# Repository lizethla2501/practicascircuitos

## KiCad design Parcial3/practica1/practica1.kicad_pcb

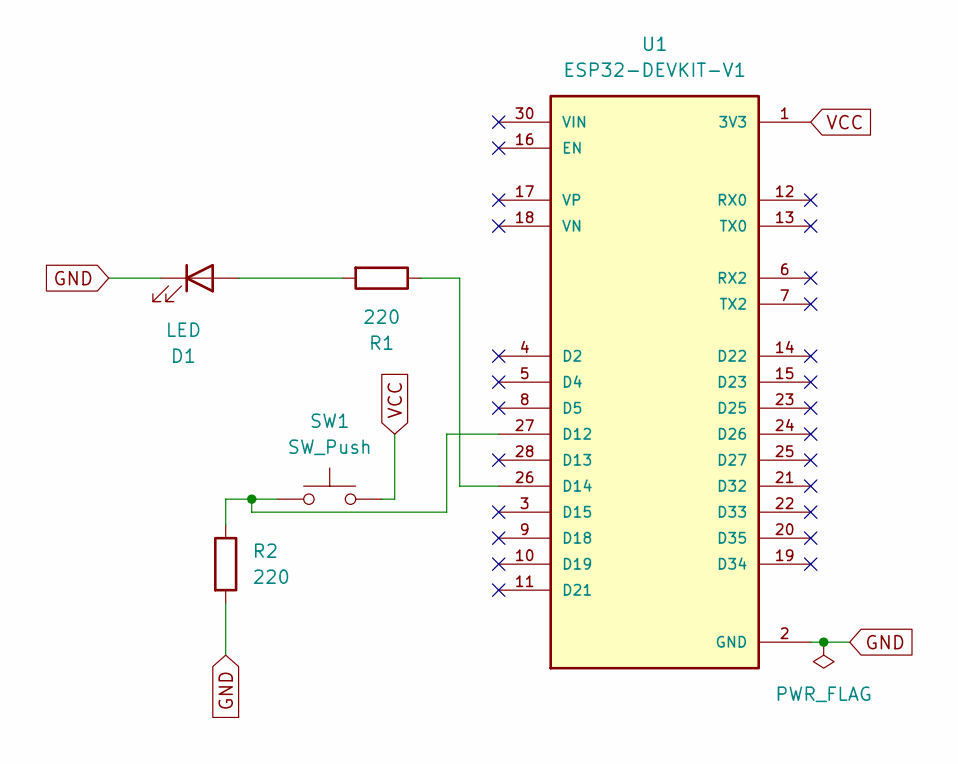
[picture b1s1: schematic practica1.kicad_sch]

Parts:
D1: LED; LED_0805_2012Metric
R1, R2: 220; R_0805_2012Metric
SW1: SW_Push; SW_Push_SPST_NO_Alps_SKRK
U1: ESP32-DEVKIT-V1; ESP32_DEVKIT_V1; PARTREV N/A

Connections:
GND: D1.1 (K), R2.2, U1.2 (GND), U1.29 (GND)
unnamed: D1.2 (A), R1.2
unnamed: R2.1, SW1.1, U1.27 (D12)
unnamed: R1.1, U1.26 (D14)
VCC: SW1.2, U1.1 (3V3)

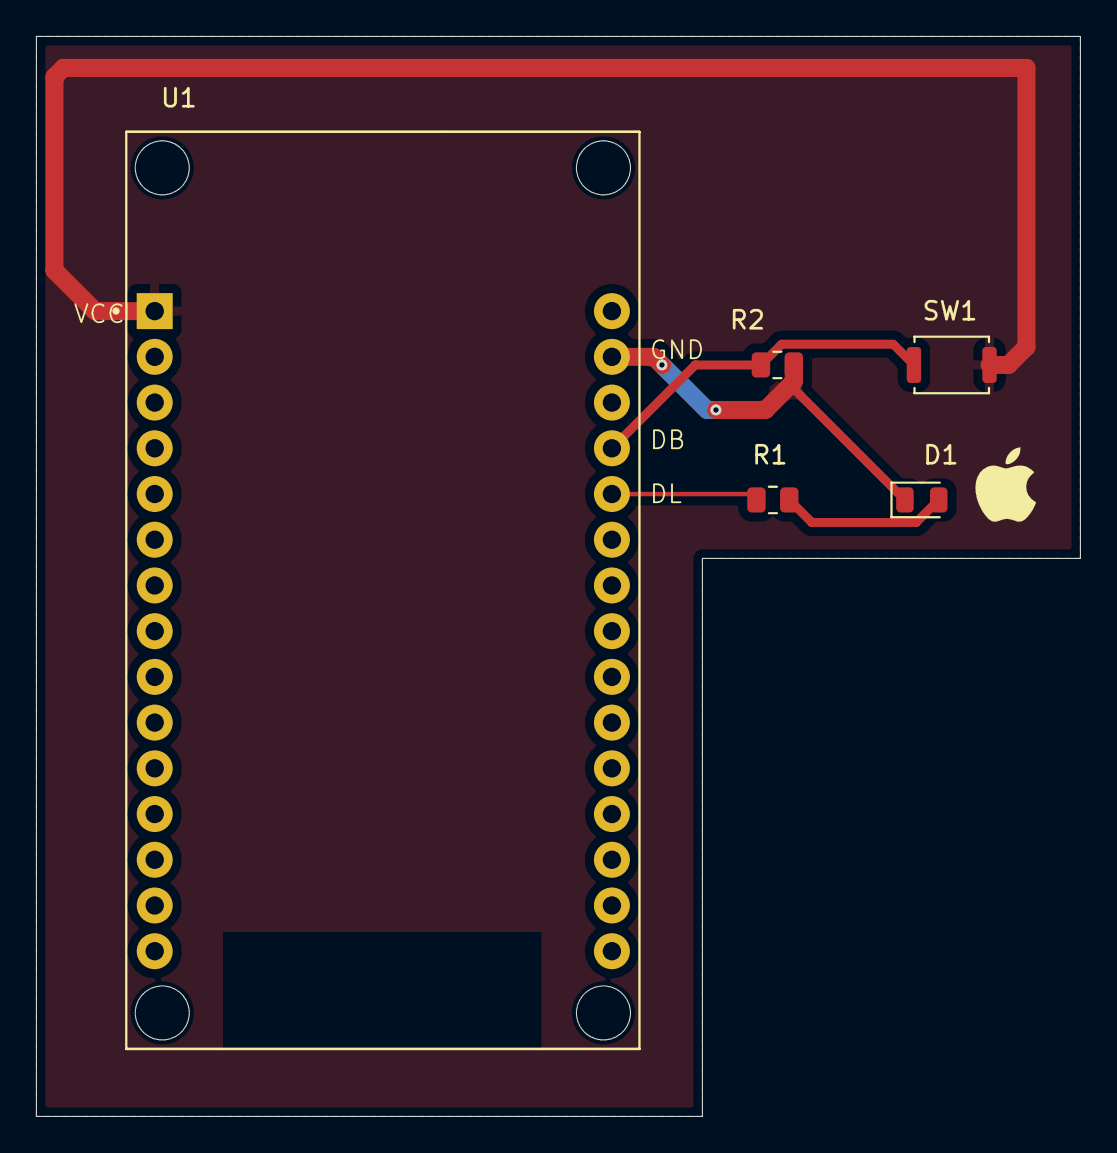
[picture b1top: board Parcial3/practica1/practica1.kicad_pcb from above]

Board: 2 copper layers, 58.0 x 60.0 mm, 5 parts (0 on the bottom side), 5 nets.

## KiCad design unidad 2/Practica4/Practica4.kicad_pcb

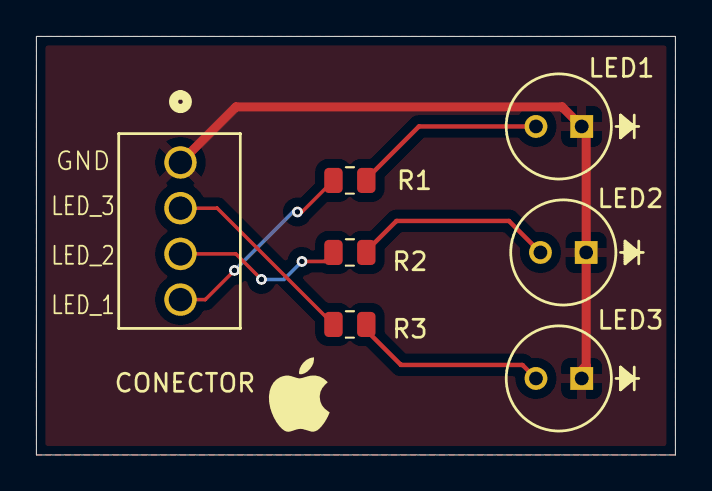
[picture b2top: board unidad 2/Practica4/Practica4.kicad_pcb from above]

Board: 2 copper layers, 35.5 x 23.2 mm, 7 parts (0 on the bottom side), 7 nets.

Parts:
CONECTOR: OSTVN04A150; TerminalBlock_CONN_OSTVN04A150_OST
LED1, LED2, LED3: LED; LED_LTL-4233_LTO
R1, R2, R3: 220; R_0805_2012Metric

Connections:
GND: CONECTOR.1, LED1.1 (K), LED2.1 (K), LED3.1 (K)
unnamed: LED1.2 (A), R1.2
unnamed: LED2.2 (A), R2.2
unnamed: LED3.2 (A), R3.2
unnamed: CONECTOR.2, R3.1
unnamed: CONECTOR.3, R2.1
unnamed: CONECTOR.4, R1.1

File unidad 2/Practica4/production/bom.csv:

Designator,Footprint,Quantity,Value,LCSC Part #
CONECTOR,TerminalBlock_CONN_OSTVN04A150_OST,1,OSTVN04A150,
"LED1, LED2, LED3",LED_LTL-4233_LTO,3,LED,
"R1, R2, R3",0805,3,220,

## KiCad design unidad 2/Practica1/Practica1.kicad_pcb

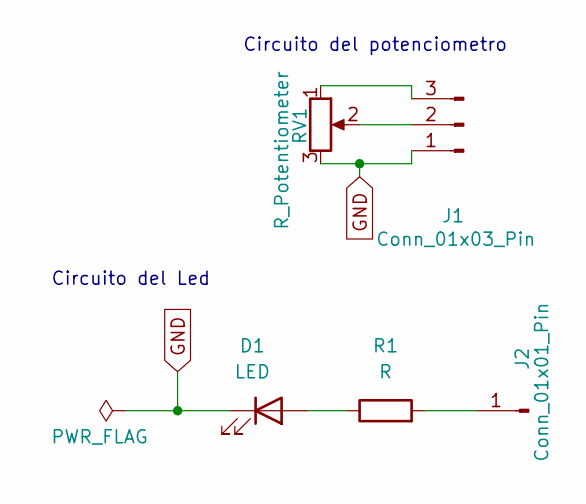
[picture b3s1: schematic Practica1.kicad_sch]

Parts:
D1: LED; LED_0805_2012Metric
J1: Conn_01x03_Pin; PinHeader_1x03_P2.54mm_Vertical
J2: Conn_01x01_Pin; PinHeader_1x01_P2.54mm_Vertical
R1: R; R_0805_2012Metric
RV1: R_Potentiometer; Potentiometer_Bourns_3339P_Vertical_HandSoldering

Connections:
GND: D1.1 (K), J1.1, RV1.3
unnamed: D1.2 (A), R1.1
unnamed: J1.2, RV1.2
unnamed: J1.3, RV1.1
unnamed: J2.1, R1.2

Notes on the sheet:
Circuito del Led
Circuito del potenciometro

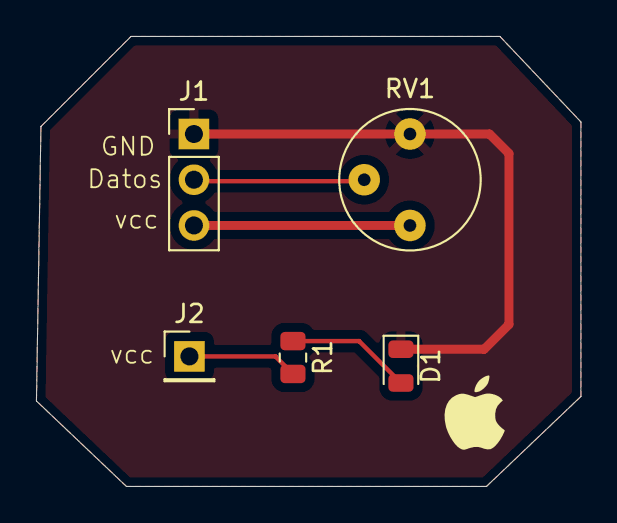
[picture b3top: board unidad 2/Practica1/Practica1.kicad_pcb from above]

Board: 2 copper layers, 30.2 x 25.0 mm, 5 parts (0 on the bottom side), 5 nets.

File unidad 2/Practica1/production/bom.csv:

Designator,Footprint,Quantity,Value,LCSC Part #
D1,0805,1,LED,
J1,PinHeader_1x03_P2.54mm_Vertical,1,Conn_01x03_Pin,
J2,PinHeader_1x01_P2.54mm_Vertical,1,Conn_01x01_Pin,
R1,0805,1,R,
RV1,Potentiometer_Bourns_3339P_Vertical_HandSoldering,1,R_Potentiometer,

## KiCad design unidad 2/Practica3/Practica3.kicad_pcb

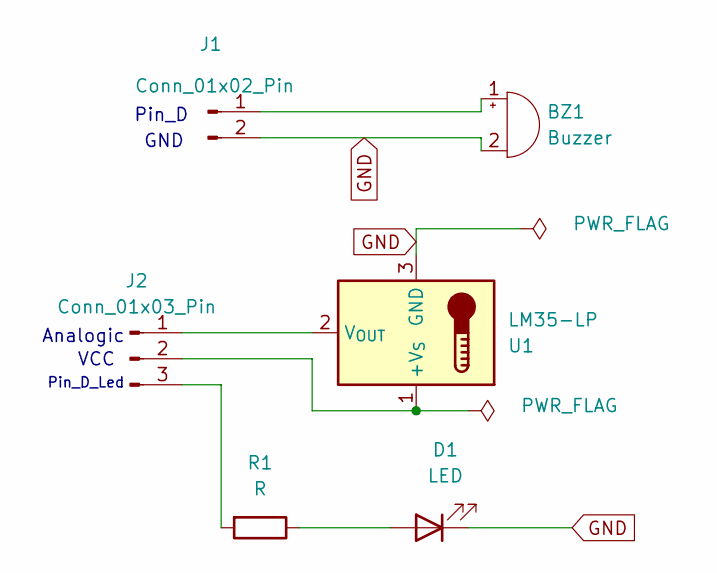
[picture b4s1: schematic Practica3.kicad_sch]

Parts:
BZ1: Buzzer; Buzzer_12x9.5RM7.6
D1: LED; LED_0805_2012Metric
J1: Conn_01x02_Pin; PinHeader_1x02_P2.54mm_Vertical
J2: Conn_01x03_Pin; PinHeader_1x03_P2.54mm_Vertical
R1: R; R_0805_2012Metric
U1: LM35-LP; TO-92_Inline

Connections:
GND: BZ1.2 (-), D1.1 (K), J1.2, U1.3 (GND)
unnamed: BZ1.1 (+), J1.1
unnamed: D1.2 (A), R1.1
unnamed: J2.1, U1.2 (V_{OUT})
unnamed: J2.2, U1.1 (+V_{S})
unnamed: J2.3, R1.2

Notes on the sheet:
Pin_D_Led
Analogic
VCC
GND
Pin_D

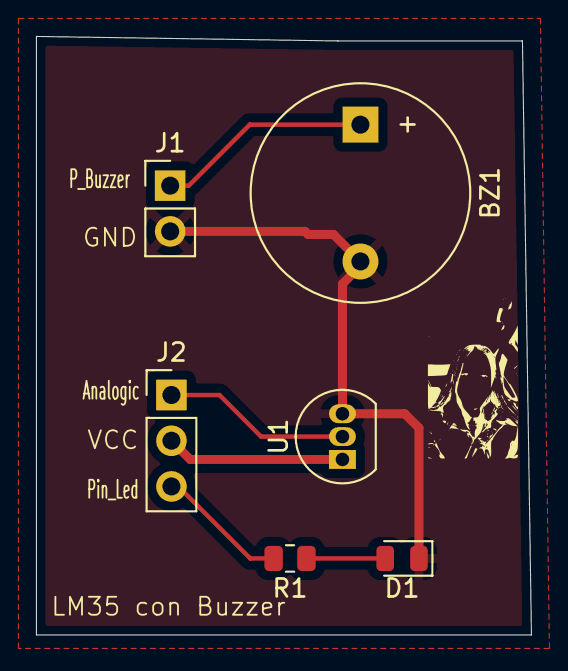
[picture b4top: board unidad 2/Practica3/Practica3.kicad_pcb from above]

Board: 2 copper layers, 27.5 x 33.2 mm, 6 parts (0 on the bottom side), 6 nets.

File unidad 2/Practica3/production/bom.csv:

Designator,Footprint,Quantity,Value,LCSC Part #
BZ1,Buzzer_12x9.5RM7.6,1,Buzzer,
D1,0805,1,LED,
J1,PinHeader_1x02_P2.54mm_Vertical,1,Conn_01x02_Pin,
J2,PinHeader_1x03_P2.54mm_Vertical,1,Conn_01x03_Pin,
R1,0805,1,R,
U1,TO-92_Inline,1,LM35-LP,

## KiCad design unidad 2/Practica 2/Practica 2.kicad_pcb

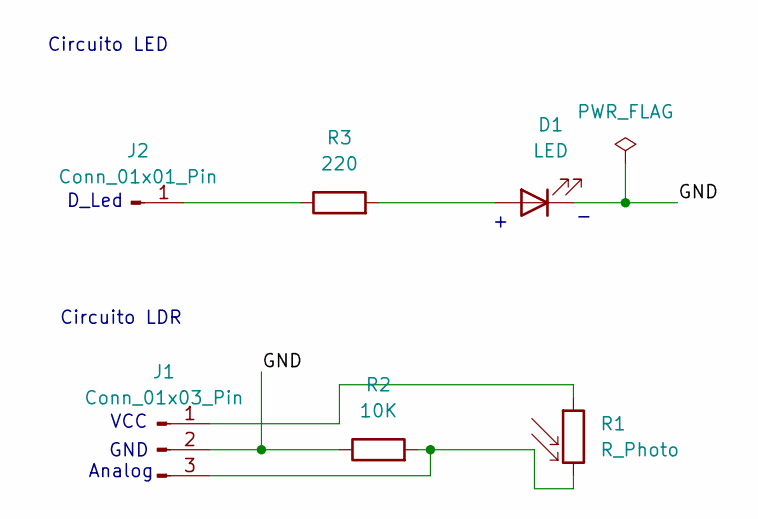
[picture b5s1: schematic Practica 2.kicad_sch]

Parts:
D1: LED; LED_0805_2012Metric
J1: Conn_01x03_Pin; PinHeader_1x03_P2.54mm_Vertical
J2: Conn_01x01_Pin; PinHeader_1x01_P2.54mm_Vertical
R1: R_Photo; R_LDR_5.1x4.3mm_P3.4mm_Vertical
R2: 10K; R_0805_2012Metric
R3: 220; R_0805_2012Metric

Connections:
/GND: D1.1 (K), J1.2, R2.1
unnamed: D1.2 (A), R3.2
unnamed: J1.1, R1.1
unnamed: J1.3, R1.2, R2.2
unnamed: J2.1, R3.1

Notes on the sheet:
Circuito LDR
Circuito LED
VCC
Analog
D_Led
GND

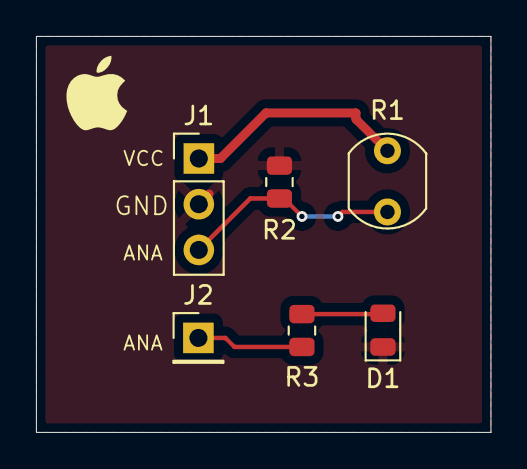
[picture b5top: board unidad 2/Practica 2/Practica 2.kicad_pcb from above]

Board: 2 copper layers, 25.2 x 22.0 mm, 6 parts (0 on the bottom side), 5 nets.

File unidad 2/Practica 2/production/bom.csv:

Designator,Footprint,Quantity,Value,LCSC Part #
D1,0805,1,LED,
J1,PinHeader_1x03_P2.54mm_Vertical,1,Conn_01x03_Pin,
J2,PinHeader_1x01_P2.54mm_Vertical,1,Conn_01x01_Pin,
R1,R_LDR_5.1x4.3mm_P3.4mm_Vertical,1,R_Photo,
R2,0805,1,10K,
R3,0805,1,220,

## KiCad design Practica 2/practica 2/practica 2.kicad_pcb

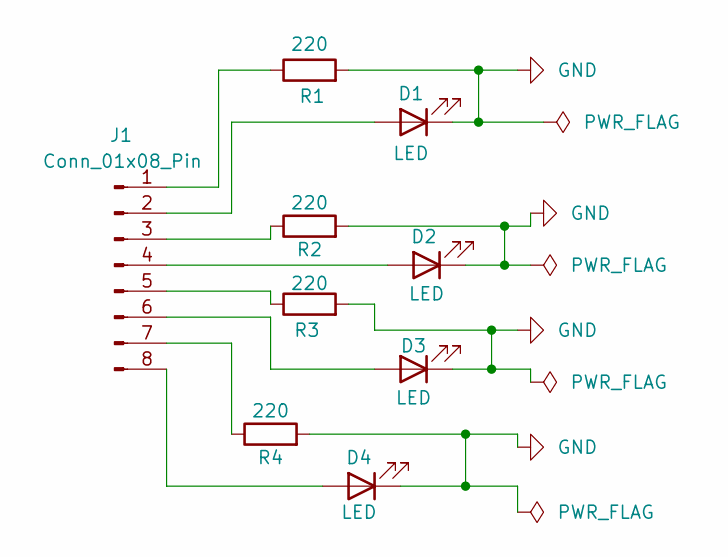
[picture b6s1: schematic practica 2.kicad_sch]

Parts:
D1, D2, D3, D4: LED; LED_0805_2012Metric
J1: Conn_01x08_Pin; PinHeader_1x08_P2.54mm_Vertical
R1, R2, R3, R4: 220; R_0805_2012Metric

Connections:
GND: D1.1 (K), D2.1 (K), D3.1 (K), D4.1 (K), R1.2, R2.2, R3.2, R4.2
unnamed: D1.2 (A), J1.2
unnamed: D2.2 (A), J1.4
unnamed: D3.2 (A), J1.6
unnamed: D4.2 (A), J1.8
unnamed: J1.1, R1.1
unnamed: J1.3, R2.1
unnamed: J1.5, R3.1
unnamed: J1.7, R4.1

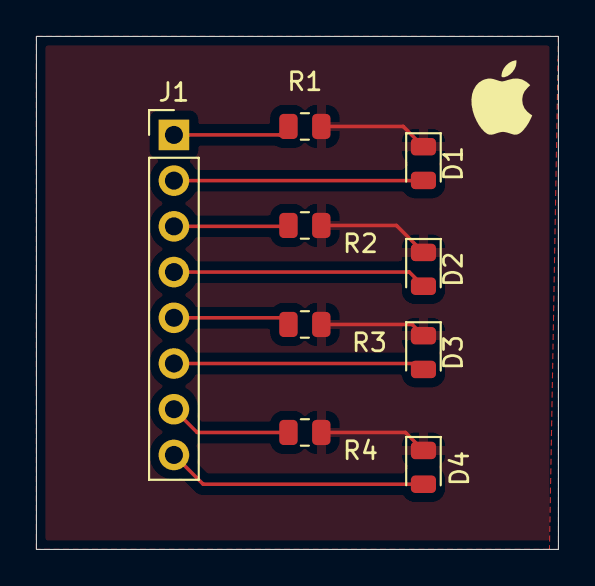
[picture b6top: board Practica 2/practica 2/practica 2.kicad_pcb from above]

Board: 2 copper layers, 29.0 x 28.5 mm, 9 parts (0 on the bottom side), 9 nets.

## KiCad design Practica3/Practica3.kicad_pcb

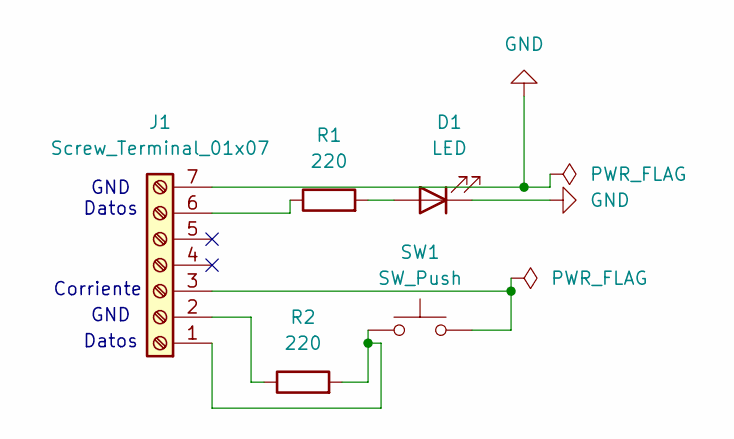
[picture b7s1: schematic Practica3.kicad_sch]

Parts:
D1: LED; LED_0805_2012Metric
J1: Screw_Terminal_01x07; TerminalBlock_Phoenix_MKDS-1,5-7_1x07_P5.00mm_Horizontal
R1, R2: 220; R_0805_2012Metric
SW1: SW_Push; SW_Push_1P1T_NO_CK_KMR2

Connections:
GND: D1.1 (K), J1.7
unnamed: D1.2 (A), R1.2
unnamed: J1.1, R2.2, SW1.1
unnamed: J1.2, R2.1
unnamed: J1.3, SW1.2
unnamed: J1.6, R1.1

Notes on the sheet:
Datos
GND
Corriente

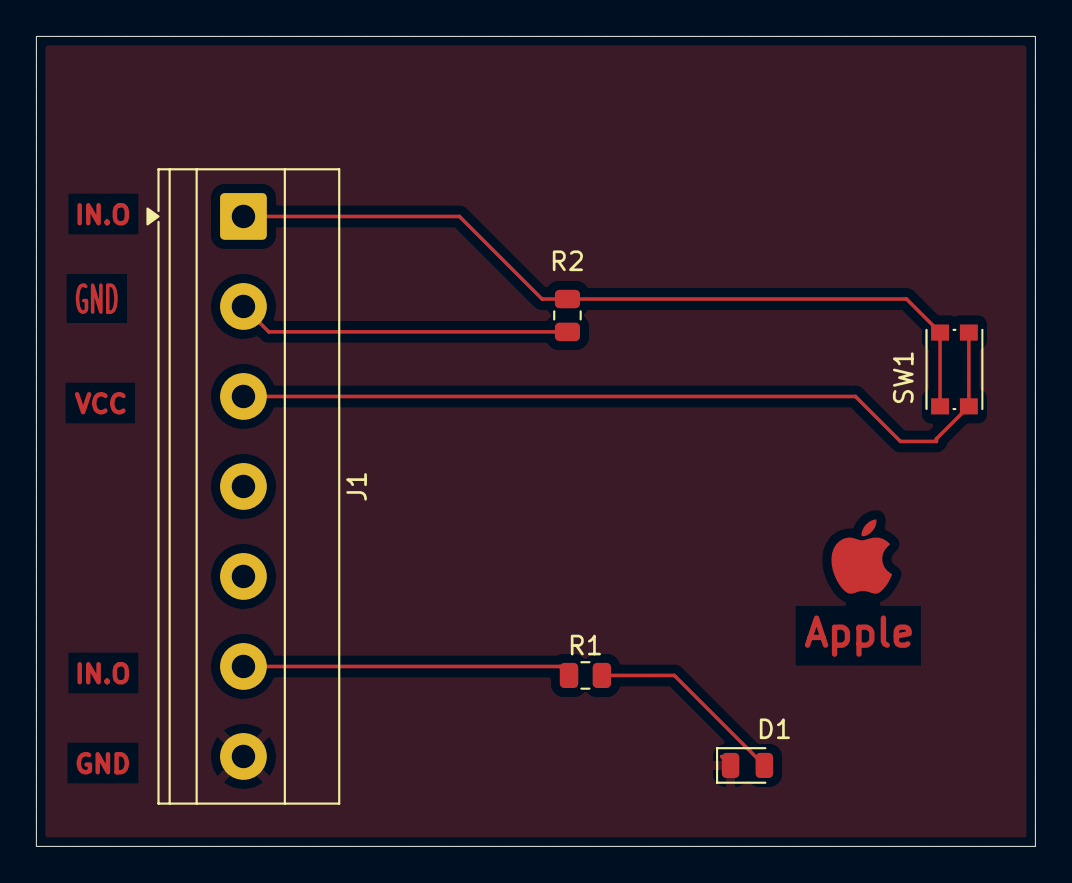
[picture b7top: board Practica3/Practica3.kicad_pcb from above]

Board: 2 copper layers, 55.5 x 45.0 mm, 5 parts (0 on the bottom side), 6 nets.

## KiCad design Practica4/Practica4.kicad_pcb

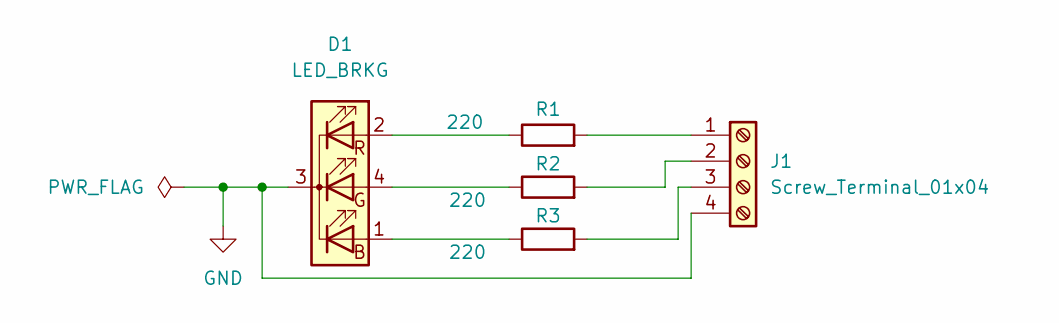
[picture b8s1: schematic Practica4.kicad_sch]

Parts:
D1: LED_BRKG; LED_RGB_1210
J1: Screw_Terminal_01x04; TerminalBlock_Phoenix_MKDS-1,5-4_1x04_P5.00mm_Horizontal
R1, R2, R3: 220; R_0805_2012Metric

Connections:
GND: D1.3 (K), J1.4
unnamed: D1.1 (BA), R3.1
unnamed: D1.4 (GA), R2.1
unnamed: D1.2 (RA), R1.1
unnamed: J1.1, R1.2
unnamed: J1.2, R2.2
unnamed: J1.3, R3.2

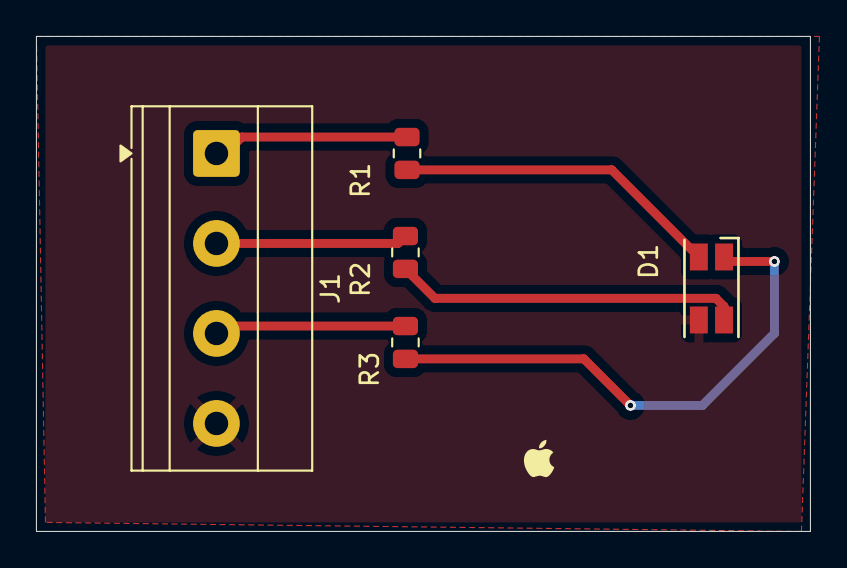
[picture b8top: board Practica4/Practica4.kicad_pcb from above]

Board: 2 copper layers, 43.0 x 27.5 mm, 5 parts (0 on the bottom side), 7 nets.

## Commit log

2026-02-10 practicas
    Practicas Unidad1
2026-03-10 parcial2
    practicas parcial2
2026-05-23 Parcial 3
    parcial 3

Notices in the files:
parts and their libraries:
COPYRIGHT: Copyright (C) 2021 Ultra Librarian. All rights reserved.
